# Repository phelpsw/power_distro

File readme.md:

## Dependencies

### Libs
 * https://github.com/phelpsw/kicad-libs
 * http://smisioto.no-ip.org/kicad_libs/library/lib_w_connectors.zip
 * http://smisioto.no-ip.org/kicad_libs/library/lib_w_transistor.zip
 * http://smisioto.no-ip.org/kicad_libs/library/lib_w_analog.zip

### Footprints
 * http://smisioto.no-ip.org/kicad_libs/modules/mod_conn_rf.zip
 * http://smisioto.no-ip.org/kicad_libs/modules/mod_smd_cap.zip
 * http://smisioto.no-ip.org/kicad_libs/modules/mod_smd_dil.zip
 * http://smisioto.no-ip.org/kicad_libs/modules/mod_smd_diode.zip
 * http://smisioto.no-ip.org/kicad_libs/modules/mod_smd_inductors.zip
 * http://smisioto.no-ip.org/kicad_libs/modules/mod_smd_leds.zip
 * http://smisioto.no-ip.org/kicad_libs/modules/mod_smd_resistors.zip
 * http://smisioto.no-ip.org/kicad_libs/modules/mod_smd_trans.zip
 * http://smisioto.no-ip.org/kicad_libs/modules/mod_conn_jst-ph.zip

### Models
 * http://smisioto.no-ip.org/kicad_libs/packages3d/3d_conn_df13.zip
 * http://smisioto.no-ip.org/kicad_libs/packages3d/3d_conn_rf.zip
 * http://smisioto.no-ip.org/kicad_libs/packages3d/3d_smd_cap.zip
 * http://smisioto.no-ip.org/kicad_libs/packages3d/3d_smd_dil.zip
 * http://smisioto.no-ip.org/kicad_libs/packages3d/3d_smd_diode.zip
 * http://smisioto.no-ip.org/kicad_libs/packages3d/3d_smd_inductors.zip
 * http://smisioto.no-ip.org/kicad_libs/packages3d/3d_smd_leds.zip
 * http://smisioto.no-ip.org/kicad_libs/packages3d/3d_smd_resistors.zip
 * http://smisioto.no-ip.org/kicad_libs/packages3d/3d_smd_trans.zip
 * http://smisioto.no-ip.org/kicad_libs/packages3d/3d_conn_jst-ph.zip

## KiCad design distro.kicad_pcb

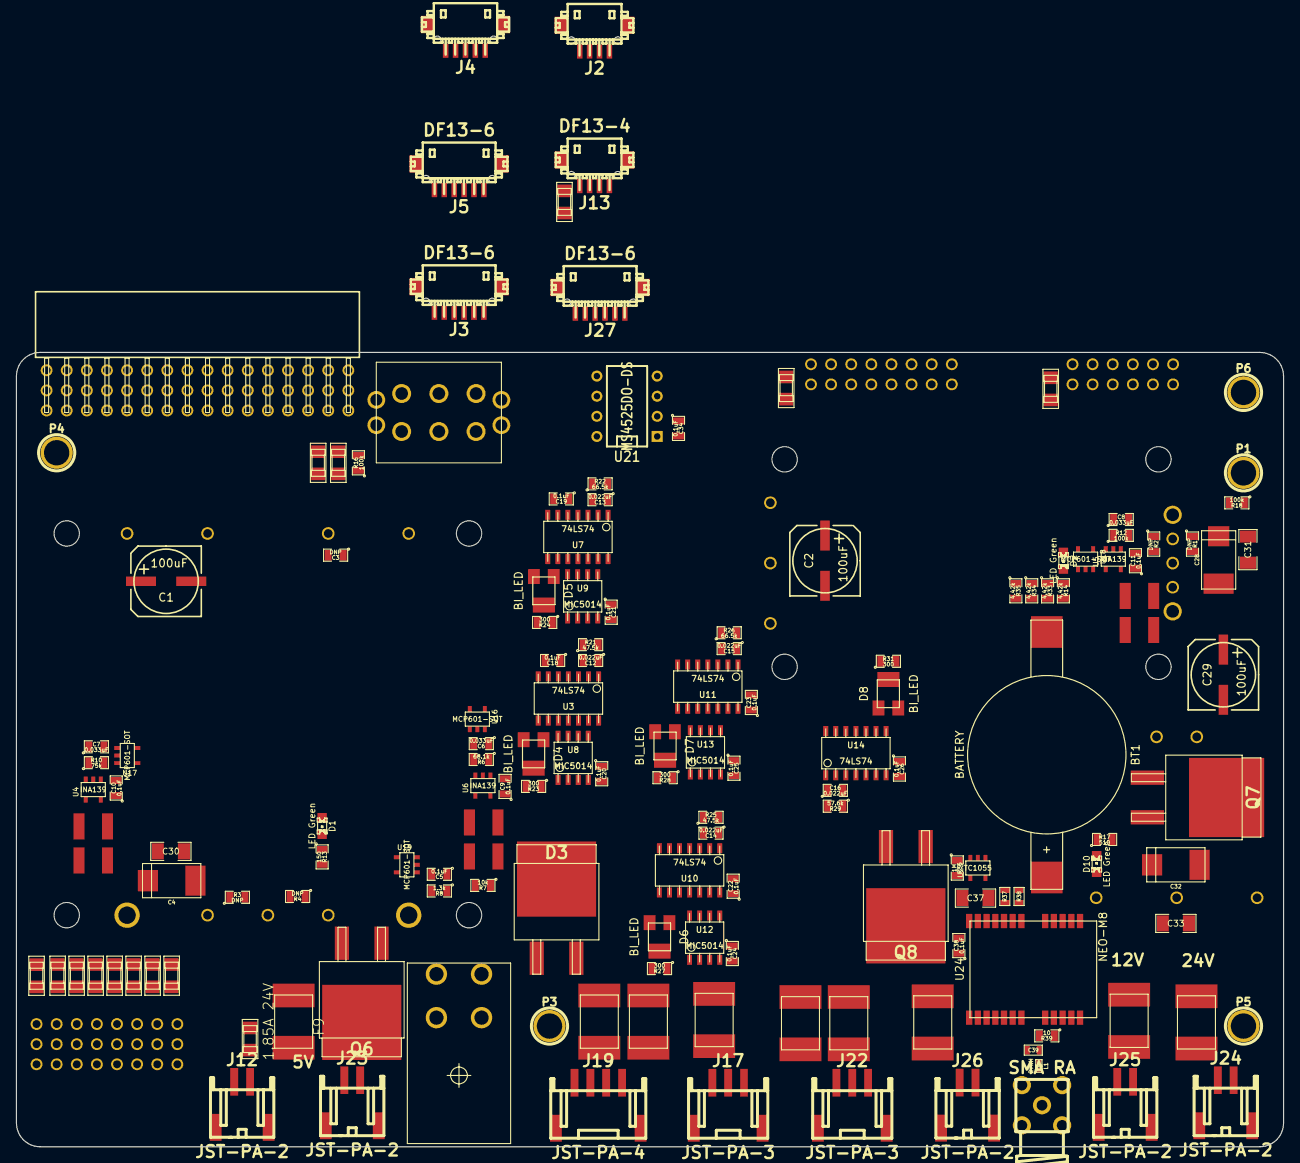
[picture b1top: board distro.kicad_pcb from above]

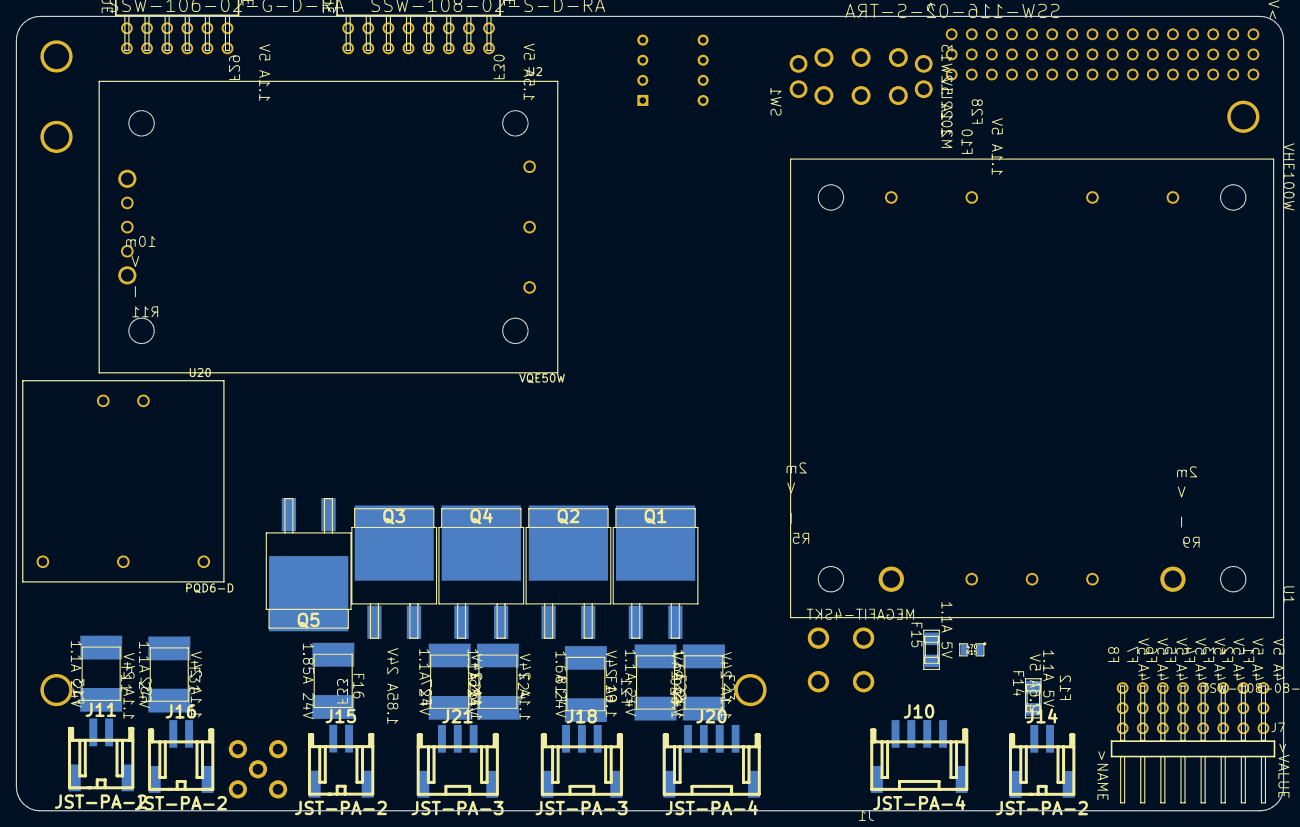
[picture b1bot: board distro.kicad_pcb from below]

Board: 2 copper layers, 160.0 x 100.3 mm, 178 parts (30 on the bottom side), 130 nets, no tracks yet.

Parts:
BT1: BATTERY; BR2032
C1, C2, C29: 100uF; SMDHD/VF
C3: DNP; SM0805
C4, C28, C32: 10uF; c_tant_V
C5, C9, C10, C11, C18, C19, C20, C21, C22, C23, C24, C25, C26, C34, C38: 0.1uF; SM0805
C6, C7, C8: 0.033uF; SM0805
C12, C13, C14, C15, C16: 0.022uF; SM0805
C30, C31, C33, C37: 1uF; SM1206
C39: 47pF; SM0603
D1, D2, D10: LED Green; LED-0805
D3: MB3045S-E3/8W; d2-pak
D4, D5, D6, D7, D8: BI_LED; LED_PLCC3
F1, F2, F3, F4, F5, F6, F7, F8: 4A 5V; littelfuse-1206
F9, F16, F33: 1.85A 24V; littelfuse-2920L
F10, F14, F15, F17, F28, F29: 1.1A 5V; littelfuse-1206
F11, F13, F20, F22, F24, F25, F26, F27, F31, F32: 1.1A 24V; littelfuse-2920L
F12: 2.6A 5V; littelfuse-1206
F18, F19, F21, F23: 1.6A 24V; littelfuse-2920L
F30: 1.5A 5V; littelfuse-1206
J1: MEGAFIT-4SKT; molex-MEGAFIT-4SKT-RA
J2, J13: DF13-4; df13-4p-125h
J3, J5, J27: DF13-6; df13-6p-125h
J4: DF13-5; df13-5p-125h
J6: SSW-116-02-S-TRA; con-samtec-SSW-116-02-S-T-RA
J7: TSW-108-08-G-T-RA; con-samtec-TSW-108-02-S-T-RA
J8: SSW-108-02-S-D-RA; con-samtec-SSW-108-02-S-D-RA
J9: SSW-106-02-G-D-RA; con-samtec-SSW-106-02-S-D-RA
J10, J19, J20: JST-PA-4; s4b-ph-sm4-tb
J11, J12, J14, J15, J16, J23, J24, J25, J26: JST-PA-2; s2b-ph-sm4-tb
J17, J18, J21, J22: JST-PA-3; s3b-ph-sm4-tb
L1: 27nH; inductor_smd_0402
P1, P3, P4, P5, P6: Pad; 1pin
P2: SMA RA; sma_90_r300.124.403
Q1, Q2, Q3, Q4, Q5, Q6, Q7, Q8: IRFZ44; d2-pak
R1, R2, R3, R4: DNP; SM0805
R5, R9: 2m; LVK25
R6: 68.1k; SM0805
R7: 10k; SM0805
R8: 1.3k; SM0805
R10: 75k; SM0805
R11: 10m; LVK25
R12, R16, R18: 100k; SM0805
R13: 150; SM0805
R14, R33, R34, R35: 4.42k; SM0805
R15: 470; SM0805
R17: 510; SM0805
R21, R25: 47.5k; SM0805
R22, R26: 66.5k; SM0805
R23, R24, R27, R28, R31: 300; SM0805
R29: 57.6k; SM0805
R36: 1M; SM0805
R37, R38: FILTER; SM0603
R39: 10; SM0805
SW1: M2022LL2W13; switch-M2022LL2W13
U1: VHE100W
U2: VQE50W
U3, U7, U10, U11, U14: 74LS74; so-14
U4, U5, U6: INA139; SOT23-5
U8, U9, U12, U13: MIC5014; so-8
U16, U17, U18, U19: MCP601-SOT; SOT23-5
U20: PQD6-D
U21: MS4525DO-DS; DIP-8__300
U23: TC1055; SOT23-5
U24: NEO-M8; NEO-M8N

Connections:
+3.3V: C37.1, C38.1, U23.5, U24.23
+5V: C9.1, C10.1, C11.1, C18.1, C19.1, C20.1, C21.1, C22.1, C23.1, C24.1, C25.1, C26.1, C34.1, D1.1, F1.1, F2.1, F3.1, F4.1, F5.1, F6.1, F7.1, F8.1, F9.2, F10.2, F12.2, F14.2, F15.2, F17.2, F28.2, F29.2, F30.2, Q7.1, R9.1, R36.1, U3.2, U3.4, U3.10, U3.13, U3.14, U4.5, U5.5, U6.5, U7.2, U7.4, U7.10, U7.13, U7.14, U8.1, U9.1, U10.2, U10.4, U10.10, U10.13, U10.14, U11.2, U11.4, U11.10, U11.13, U11.14, U12.1, U13.1, U14.2, U14.4, U14.10, U14.13, U14.14, U16.5, U17.5, U18.5, U19.5, U21.2, U23.1
+12V: C32.1, C33.1, D10.1, F31.2, F32.2, F33.2, U20.3
+24V: D2.1, F11.2, F13.2, F16.2, R11.1
+BATT: C1.1, C2.1, C29.1, Q1.2, Q2.2, Q3.2, Q4.2, R5.1, U1.1, U2.1, U20.2
/Identification Lights/RC_IN: U3.3, U3.12, U7.3, U7.12
/Identification Lights/STROBE: F18.2, F19.2, F21.2, F23.2, Q2.3, U9.3
/Identification Lights/SYNC: J17.3, J18.3, J19.4, J20.4
/Identification Lights/WING_LIGHT: F20.2, F22.2, Q1.3, U8.3
/Landing Lights/LANDING: F24.2, F26.2, Q4.3, U13.3
/Landing Lights/RC_IN: U10.3, U10.12, U11.3, U11.12
/Landing Lights/TAXI: F25.2, F27.2, Q3.3, U12.3
/Lidar/AUX5 (Mode): J10.3, R15.1
/Payload/Payload_Switched: D8.1, Q5.1, Q6.1, Q8.1, U14.9
/Payload/RC_IN: U14.3, U14.12
/Pixhawk/5V_CURR_MEAS: J4.2, U17.1, U17.4
/Pixhawk/24V_CURR_MEAS: J4.4, U18.1, U18.4
/Pixhawk/FMAIN1_5V: F1.2, J7.2
/Pixhawk/FMAIN2_5V: F2.2, J7.5
/Pixhawk/FMAIN3_5V: F3.2, J7.8
/Pixhawk/FMAIN4_5V: F4.2, J7.11
/Pixhawk/FMAIN5_5V: F5.2, J7.14
/Pixhawk/FMAIN6_5V: F6.2, J7.17
/Pixhawk/FMAIN7_5V: F7.2, J7.20
/Pixhawk/FMAIN8_5V: F8.2, J7.23
/Pixhawk/MAIN1: J6.30, J7.3
/Pixhawk/MAIN2: J6.27, J7.6
/Pixhawk/MAIN3: J6.24, J7.9
/Pixhawk/MAIN4: J6.21, J7.12
/Pixhawk/MAIN5: J6.18, J7.15
/Pixhawk/MAIN6: J6.15, J7.18
/Pixhawk/MAIN7: J6.12, J7.21
/Pixhawk/MAIN8: J6.9, J7.24
/Pixhawk/MEAS_CURRENT: J3.3, U16.1, U16.4
/Pixhawk/MEAS_VOLTAGE: J3.4, U19.1, U19.4
/Pixhawk/RC_SIG: J6.3, J9.1
/Power/5V_ONOFF: SW1.P2, U1.2
/Power/24V_ONOFF: SW1.P5, U2.2
GND: BT1.2, C1.2, C2.2, C3.1, C4.2, C5.2, C6.2, C7.1, C8.1, C9.2, C10.2, C11.2, C12.2, C13.2, C14.2, C15.2, C16.2, C18.2, C19.2, C20.2, C21.2, C22.2, C23.2, C24.2, C25.2, C26.2, C28.2, C30.2, C31.2, C32.2, C33.2, C34.2, C37.2, C38.2, C39.2, J1.3, J1.4, J2.4, J3.5, J3.6, J4.3, J4.5, J5.6, J6.1, J6.4, J6.7, J6.10, J6.13, J6.16, J6.19, J6.22, J6.25, J6.28, J6.31, J6.34, J6.37, J6.40, J6.43, J6.46, J7.1, J7.4, J7.7, J7.10, J7.13, J7.16, J7.19, J7.22, J8.1, J9.5, J10.4, J11.2, J12.2, J13.4, J14.2, J16.2, J17.2, J18.2, J19.3, J20.3, J21.3, J22.3, J24.2, J25.2, J27.6, P2.2, Q5.3, Q6.3, Q7.3, Q8.3, R2.1, R4.1, R6.2, R8.2, R10.1, R12.1, R13.2, R14.2, R15.2, R16.2, R17.2, R18.2, R23.2, R24.2, R27.2, R28.2, R31.2, R33.2, R34.2, R35.2, SW1.P1, SW1.P4, U1.4, U1.5, U1.6, U2.3, U2.4, U2.5, U3.7, U4.2, U5.2, U6.2, U7.7, U8.4, U9.4, U10.7, U11.7, U12.4, U13.4, U14.7, U16.2, U17.2, U18.2, U19.2, U20.5, U21.1, U23.2, U24.7, U24.10, U24.12, U24.13, U24.24
unnamed: R11.3, U5.4
unnamed: R11.4, U5.3
unnamed: D1.2, R13.1
unnamed: R9.3, U4.4
unnamed: R9.4, U4.3
unnamed: R3.2, R4.2, U1.7
unnamed: C3.2, U1.3
unnamed: R1.2, R2.2, U2.6
unnamed: R16.1, SW1.GND1, SW1.GND2, SW1.GND3, SW1.GND4
unnamed: C28.1, C31.1, R1.1, R11.2, U2.7, U2.8
unnamed: C4.1, C30.1, R3.1, R9.2, U1.8, U1.9
unnamed: R36.2, U23.4
unnamed: C29.2, Q7.2, U20.1
unnamed: D10.2, R17.1
unnamed: C8.2, R12.2, U5.1, U18.3
unnamed: C6.1, R6.1, U6.1, U16.3
unnamed: R5.4, U6.3
unnamed: R5.3, U6.4
unnamed: D3.2, R5.2, R7.1
unnamed: C5.1, R7.2, R8.1, U19.3
unnamed: C7.2, R10.2, U4.1, U17.3
unnamed: D3.1, J1.1, J1.2
unnamed: D2.2, R14.1, R33.1, R34.1, R35.1
unnamed: F28.1, J3.1, J3.2
unnamed: BT1.1, U24.22
unnamed: R37.2, U24.21
unnamed: R39.1, U24.9
unnamed: C39.1, L1.1, R39.2
unnamed: L1.2, P2.1, U24.11
unnamed: J27.3, R38.1
unnamed: R38.2, U24.20
unnamed: J27.2, R37.1
unnamed: J2.2, J13.2, U21.4
unnamed: J2.3, J13.3, U21.3
unnamed: F17.1, J13.1
unnamed: F10.1, J6.2, J6.5, J6.8, J6.11, J6.14, J6.17, J6.20, J6.23, J6.26, J6.29, J6.32, J6.35, J6.38, J6.41, J6.44, J6.47
unnamed: J8.4, J8.6
unnamed: F30.1, J8.5
unnamed: F29.1, J9.3
unnamed: F18.1, J17.1
unnamed: F21.1, J19.2
unnamed: F20.1, J19.1
unnamed: F19.1, J18.1
unnamed: D5.2, R24.1
unnamed: D5.3, U7.8
unnamed: Q1.1, U8.5
unnamed: D5.1, U7.9, U9.2
unnamed: D4.2, R23.1
unnamed: D4.1, U3.9, U8.2
unnamed: D4.3, U3.8
unnamed: F23.1, J20.2
unnamed: F22.1, J20.1
unnamed: C13.1, R22.2, U7.1
unnamed: R22.1, U7.6, U7.11
unnamed: C12.1, R21.2, U3.1
unnamed: Q2.1, U9.5
unnamed: R21.1, U3.6, U3.11
unnamed: D6.3, U10.8
unnamed: D6.2, R27.1
unnamed: D7.1, U11.9, U13.2
unnamed: D7.3, U11.8
unnamed: D7.2, R28.1
unnamed: F24.1, J21.1
unnamed: F25.1, J21.2
unnamed: D6.1, U10.9, U12.2
unnamed: Q3.1, U12.5
unnamed: F27.1, J22.2
unnamed: F26.1, J22.1
unnamed: C15.1, R26.2, U11.1
unnamed: R26.1, U11.6, U11.11
unnamed: R25.1, U10.6, U10.11
unnamed: C14.1, R25.2, U10.1
unnamed: Q4.1, U13.5
unnamed: F15.1, J10.1
unnamed: F11.1, J11.1
unnamed: F14.1, J14.1
unnamed: F12.1, J12.1
unnamed: F13.1, J24.1
unnamed: F31.1, J16.1
unnamed: F33.1, J26.1
unnamed: J26.2, Q8.2
unnamed: F32.1, J25.1
unnamed: R29.1, U14.6, U14.11
unnamed: D8.3, U14.8
unnamed: D8.2, R31.1
unnamed: J23.2, Q6.2
unnamed: C16.1, R29.2, U14.1
unnamed: F9.1, J23.1
unnamed: J15.2, Q5.2
unnamed: F16.1, J15.1
unnamed: P1.1, R18.1

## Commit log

2015-08-14 Initial cut at this board schematic using kicad.
2015-08-21 Adding gitignore file for backup files.
2015-08-21 Continued syncing with original design.
2015-08-21 Including readme.
2015-08-22 Finishing bom integration with schematic.
2015-08-22 Adding buffer on voltage reference output.
2015-08-22 Fixing number on new buffer.
2015-08-22 Updating design with new 12v bus.
2015-08-25 Adding gps receiver, updating netlist and completing component assignment.
2015-08-26 Updating layout and component pad configs.
2015-08-28 Preliminary layout complete.
